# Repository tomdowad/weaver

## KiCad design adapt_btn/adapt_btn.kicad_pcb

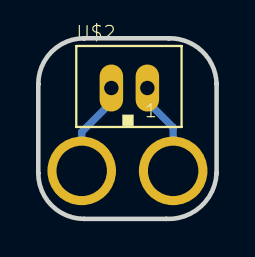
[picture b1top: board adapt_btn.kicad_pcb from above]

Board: 2 copper layers, 9.9 x 10.0 mm, 3 parts (0 on the bottom side), 2 nets.

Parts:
U$1, U$3: BUTTON_PAD
U$2: JST-PH_2-PIN_HEADER; JST_B2B-PH_HEADER

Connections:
unnamed: U$2.P1, U$3.P$1
unnamed: U$1.P$1, U$2.P2

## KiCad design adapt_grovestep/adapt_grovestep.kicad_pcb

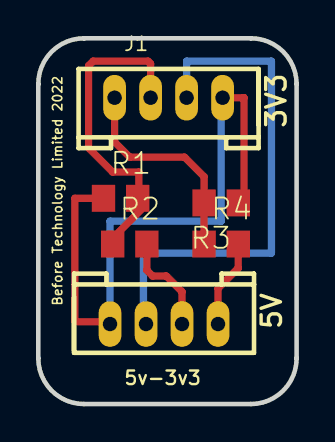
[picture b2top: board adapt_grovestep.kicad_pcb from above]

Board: 2 copper layers, 14.4 x 20.3 mm, 6 parts (0 on the bottom side), 6 nets.

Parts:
J1, J2: 4P-2.0; HW4-2.0
R1, R2, R3, R4: R0805

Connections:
unnamed: J1.2, R1.2, R2.1
unnamed: J1.1, R3.2, R4.1
unnamed: J1.4, J2.4, R1.1, R3.1
unnamed: J1.3, J2.3
unnamed: J2.2, R2.2
unnamed: J2.1, R4.2

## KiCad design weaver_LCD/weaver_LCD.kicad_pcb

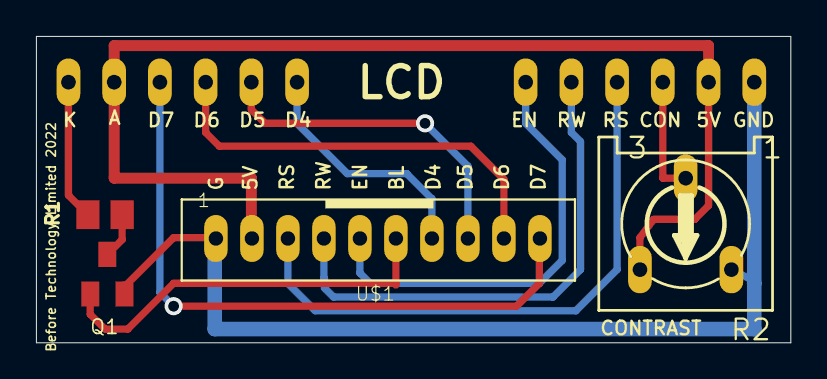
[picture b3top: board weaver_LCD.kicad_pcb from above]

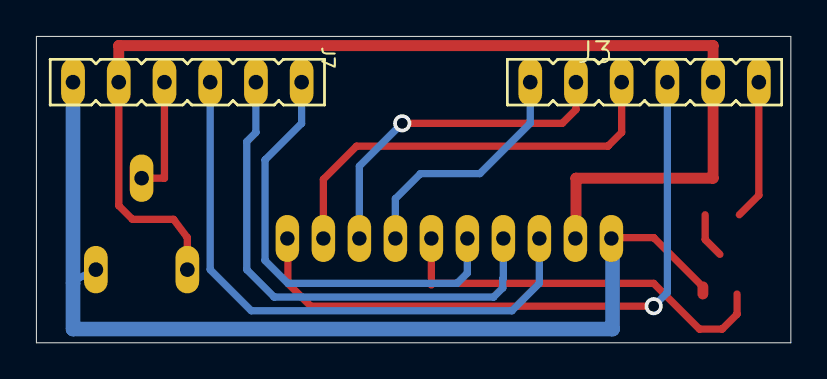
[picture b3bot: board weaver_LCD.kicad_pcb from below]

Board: 2 copper layers, 41.9 x 17.0 mm, 6 parts (2 on the bottom side), 13 nets.

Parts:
J3, J7: FE06
Q1: BSS123; SOT23
R1: 100; M0805
R2: RS3
U$1: JST-PH_10-PIN_HEADER; JST_B10B-PH_HEADER

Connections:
+5V: J3.5, J7.2, R2.E, U$1.P2
BL: Q1.1, U$1.P6
CONTRAST: J7.3, R2.S
EN: J7.6, U$1.P5
GND: J7.1, Q1.2, R2.A, U$1.P1
unnamed: Q1.3, R1.1
unnamed: J3.1, U$1.P7
unnamed: J3.2, U$1.P8
unnamed: J3.3, U$1.P9
unnamed: J3.4, U$1.P10
unnamed: J3.6, R1.2
RS: J7.4, U$1.P3
RW: J7.5, U$1.P4

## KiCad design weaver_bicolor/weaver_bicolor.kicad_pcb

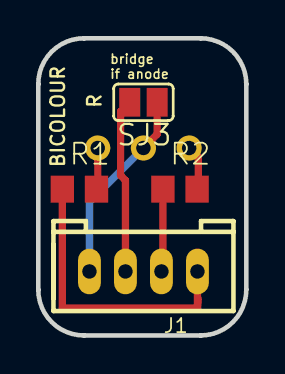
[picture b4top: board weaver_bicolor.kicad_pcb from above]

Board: 2 copper layers, 11.6 x 16.5 mm, 5 parts (1 on the bottom side), 6 nets.

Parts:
J1: 4P-2.0; HW4-2.0
LED2: L-59EGW-CA
R1: 220; R0805
R2: 1k2; R0805
SJ3: SJ

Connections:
GND: J1.4, LED2.2, SJ3.1
unnamed: LED2.1, R1.2
unnamed: LED2.3, R2.2
unnamed: J1.1, R1.1
unnamed: J1.2, R2.1
unnamed: J1.3, SJ3.2

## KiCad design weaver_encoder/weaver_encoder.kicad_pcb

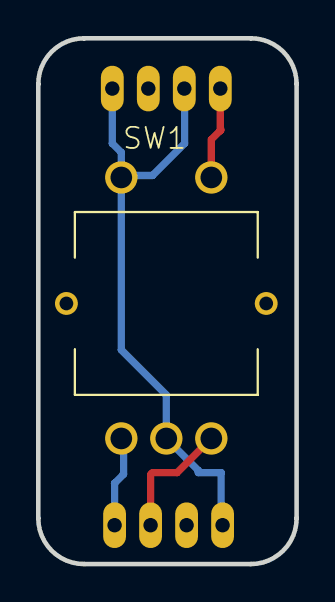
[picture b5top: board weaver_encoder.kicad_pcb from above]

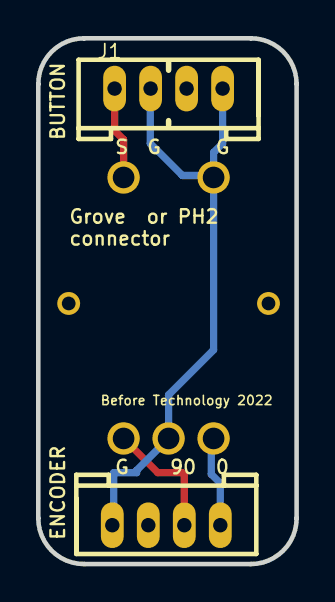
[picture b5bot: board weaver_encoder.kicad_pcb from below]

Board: 2 copper layers, 14.4 x 29.2 mm, 3 parts (2 on the bottom side), 4 nets.

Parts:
J1, J2: 4P-2.0; HW4-2.0
SW1: SWITCH-ALPS_EC12E_SW; SWITCH-ALPS_ALPS_EC12E_SW

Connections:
GND: J1.2, J1.4, J2.4, SW1.C, SW1.D
unnamed: J2.1, SW1.A
unnamed: J2.2, SW1.B
unnamed: J1.1, SW1.E

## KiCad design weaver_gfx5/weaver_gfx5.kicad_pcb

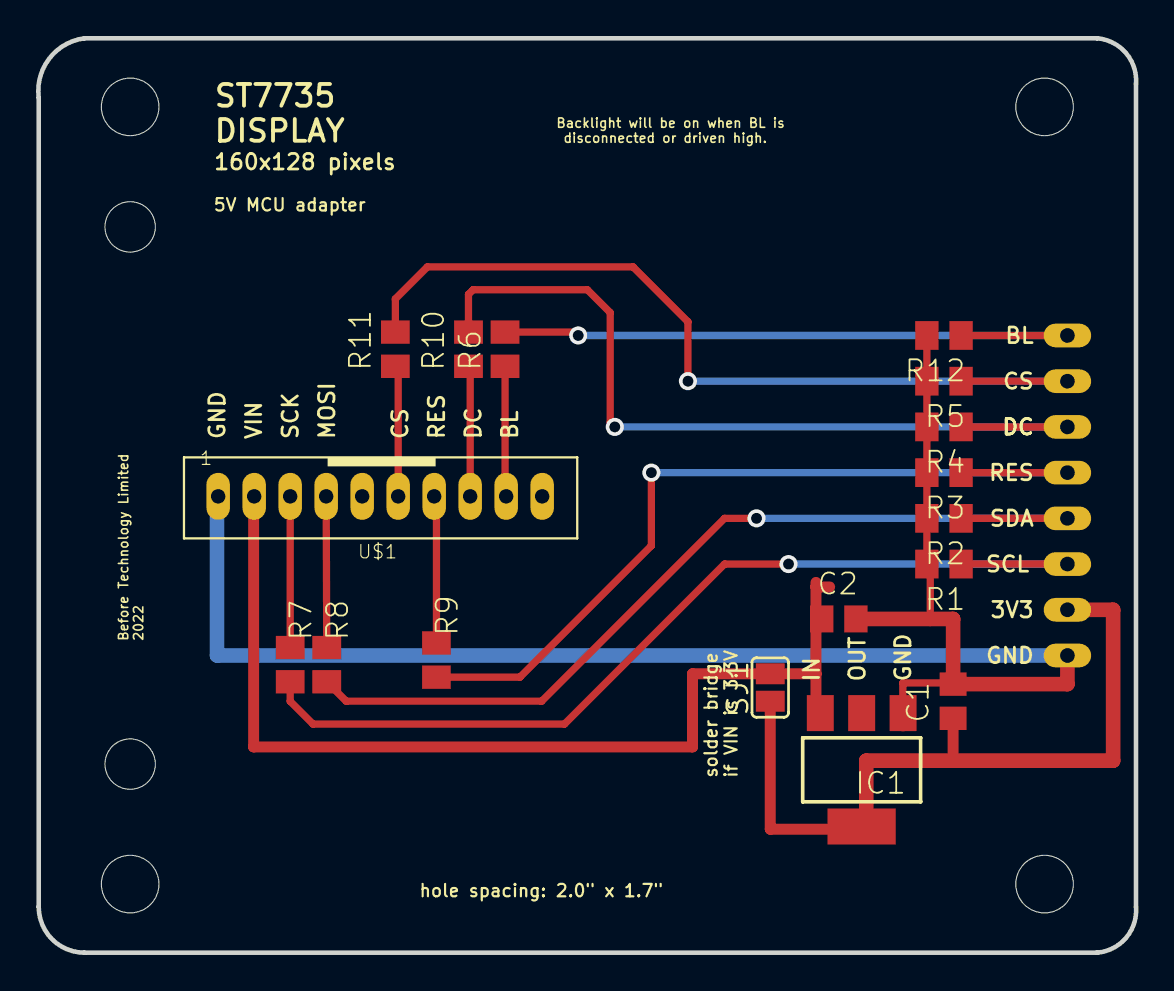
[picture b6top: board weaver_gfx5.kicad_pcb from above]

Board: 2 copper layers, 61.0 x 50.8 mm, 24 parts (1 on the bottom side), 15 nets.

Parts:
@HOLE0, @HOLE1, @HOLE2, @HOLE3, @HOLE4, @HOLE5: (no value)
C1, C2: C0805
IC1: LD117AS18TR; SOT223
R1, R2, R3, R4, R5, R6, R7, R8, R9, R10, R11, R12: M0805
SJ1: SJ
SV2: FE08
U$1: JST-PH_10-PIN_HEADER; JST_B10B-PH_HEADER

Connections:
BL5: R6.1, U$1.P9
BLK: R6.2, R12.1, SV2.8
CS3: R5.1, R11.2, SV2.7
CS5: R11.1, U$1.P6
DC3: R4.1, R10.2, SV2.6
DC5: R10.1, U$1.P8
GND: C1.2, C2.2, IC1.1, R1.2, R2.2, R3.2, R4.2, R5.2, R12.2, SV2.1, U$1.P1
MOSI: R8.1, U$1.P4
unnamed: C2.1, IC1.3, SJ1.2, U$1.P2
unnamed: C1.1, IC1.4, SJ1.1, SV2.2
RST3: R3.1, R9.2, SV2.5
RST5: R9.1, U$1.P7
SCK3: R1.1, R7.2, SV2.3
SCK5: R7.1, U$1.P3
SDA3: R2.1, R8.2, SV2.4

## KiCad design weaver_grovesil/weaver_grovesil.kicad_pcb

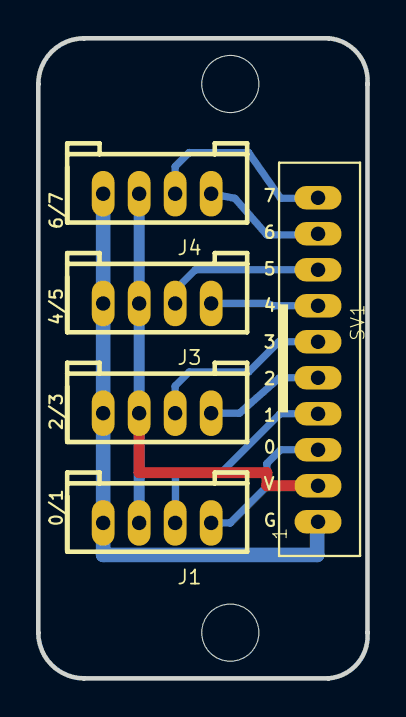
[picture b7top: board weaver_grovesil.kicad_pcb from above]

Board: 2 copper layers, 18.3 x 35.6 mm, 7 parts (0 on the bottom side), 10 nets.

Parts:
@HOLE0, @HOLE1: (no value)
J1, J2, J3, J4: 4P-2.0; HW4-2.0
SV1: JST-PH_10-PIN_HEADER; JST_B10B-PH_HEADER

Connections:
GND: J1.4, J2.4, J3.4, J4.4, SV1.P1
unnamed: J1.3, J2.3, J3.3, J4.3, SV1.P2
unnamed: J1.1, SV1.P3
unnamed: J1.2, SV1.P4
unnamed: J2.1, SV1.P5
unnamed: J2.2, SV1.P6
unnamed: J3.1, SV1.P7
unnamed: J3.2, SV1.P8
unnamed: J4.1, SV1.P9
unnamed: J4.2, SV1.P10
